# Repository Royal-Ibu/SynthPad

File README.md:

# SynthPad
A custom MIDI keypad with 6 Kalih Choc switches, an EC11 Rotary Encoder, a Bourns slide potentiometer, capacitive touch keys, and a Waveshare ESP32-S3-ZERO! SynthPad was made as a submission for Hack Club's Half-Life Week 3 Challenge - Music Projects!

## Renders

## Features

- Six Kailh Choc switches: Six low-profile mechanical keys for tactile input.
- EC11 rotary encoder: Provides rotary input and an integrated push-button input.
- Bourns slide potentiometer: Adds a sliding analog control for a MIDI parameter.
- Waveshare ESP32-S3-ZERO: Handles the controller's inputs and will run the MIDI firmware.
- Capacitive touch keys: Electronic touch pad switches for further inputs!

## Bill of Materials (BOM)

| Component | Quantity | Description | Part / model |
|---|---:|---|---|
| Kailh Choc switches | 6 | Low-profile mechanical key switches | Exact variant TBD |
| EC11 rotary encoder | 1 | Incremental rotary encoder with push-button input | Exact variant TBD |
| Bourns slide potentiometer | 1 | Linear slide potentiometer for analog input | Exact part number TBD |
| Waveshare ESP32-S3-ZERO | 1 | Main microcontroller board | ESP32-S3-ZERO |
| 1N4148 Diodes | 6 | Through-hole diodes, one per switch | TBD |

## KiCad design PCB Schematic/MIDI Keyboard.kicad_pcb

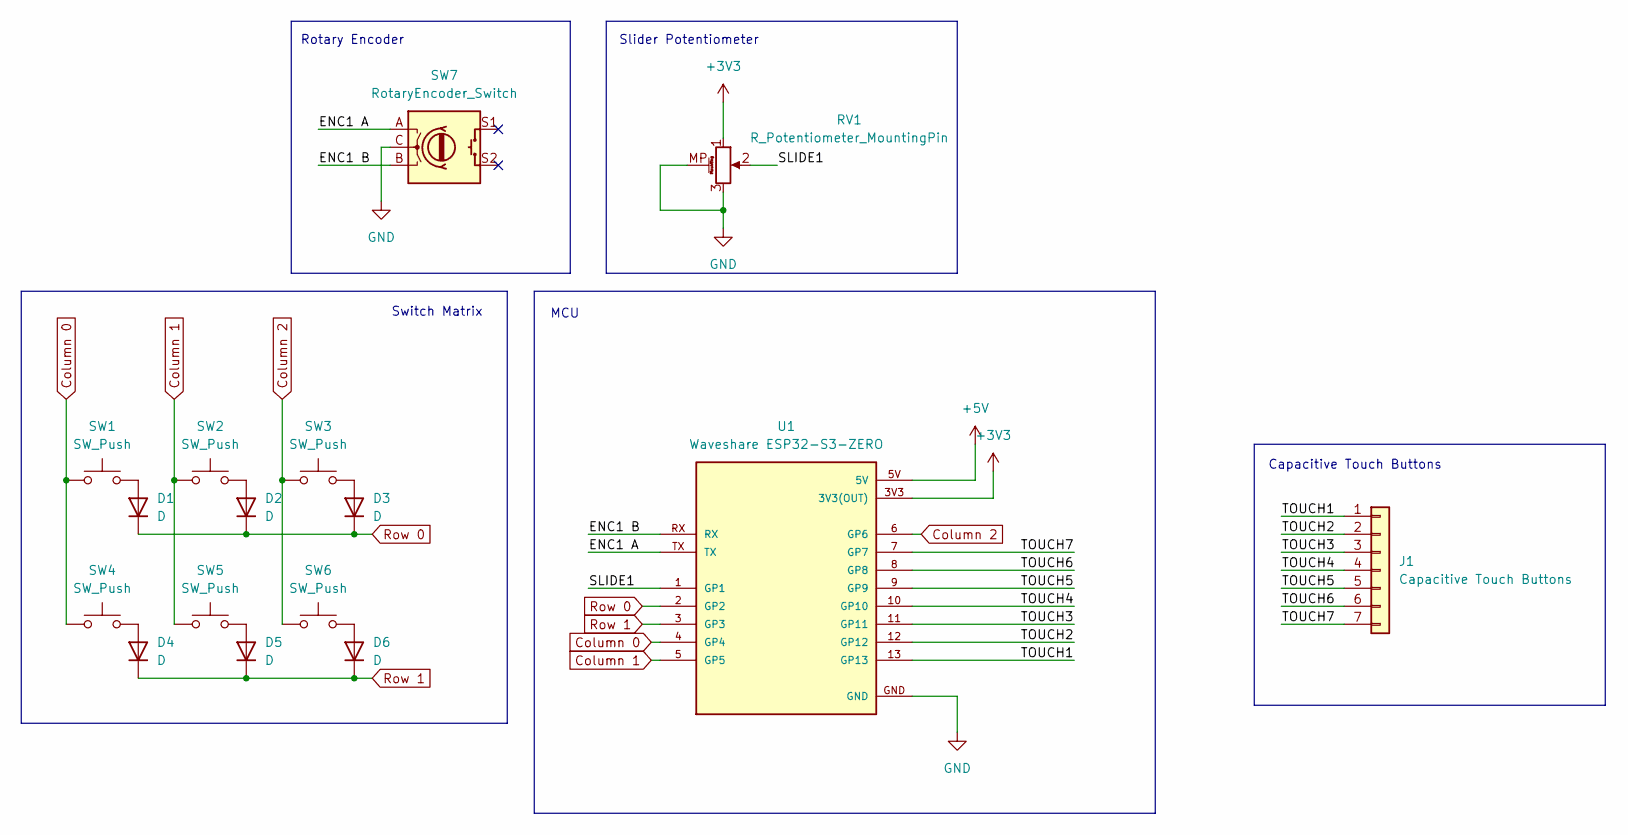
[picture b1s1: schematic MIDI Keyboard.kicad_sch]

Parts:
D1, D2, D3, D4, D5, D6: D; D_DO-35_SOD27_P7.62mm_Horizontal
J1: Capacitive Touch Buttons; Capacitive Keys
RV1: R_Potentiometer_MountingPin; Potentiometer_Bourns_PTA1543_Single_Slide
SW1, SW2, SW3, SW4, SW5, SW6: SW_Push; Kailh Choc Low-Profile Switches
SW7: RotaryEncoder_Switch; RotaryEncoder_Alps_EC11E-Switch_Vertical_H20mm
U1: Waveshare ESP32-S3-ZERO; Waveshare ESP32-S3-Zero; PARTREV NA

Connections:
+3V3: RV1.1, U1.3V3 (3V3(OUT))
+5V: U1.5V
/ENC1 A: SW7.A, U1.TX
/ENC1 B: SW7.B, U1.RX
/SLIDE1: RV1.2, U1.1 (GP1)
/TOUCH1: J1.1, U1.13 (GP13)
/TOUCH2: J1.2, U1.12 (GP12)
/TOUCH3: J1.3, U1.11 (GP11)
/TOUCH4: J1.4, U1.10 (GP10)
/TOUCH5: J1.5, U1.9 (GP9)
/TOUCH6: J1.6, U1.8 (GP8)
/TOUCH7: J1.7, U1.7 (GP7)
Column 0: SW1.1, SW4.1, U1.4 (GP4)
Column 1: SW2.1, SW5.1, U1.5 (GP5)
Column 2: SW3.1, SW6.1, U1.6 (GP6)
GND: RV1.3, RV1.MP (MountPin), SW7.C, U1.GND
unnamed: D1.2 (A), SW1.2
unnamed: D2.2 (A), SW2.2
unnamed: D3.2 (A), SW3.2
unnamed: D4.2 (A), SW4.2
unnamed: D5.2 (A), SW5.2
unnamed: D6.2 (A), SW6.2
Row 0: D1.1 (K), D2.1 (K), D3.1 (K), U1.2 (GP2)
Row 1: D4.1 (K), D5.1 (K), D6.1 (K), U1.3 (GP3)

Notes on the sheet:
Switch Matrix
Slider Potentiometer
Capacitive Touch Buttons
Rotary Encoder
MCU

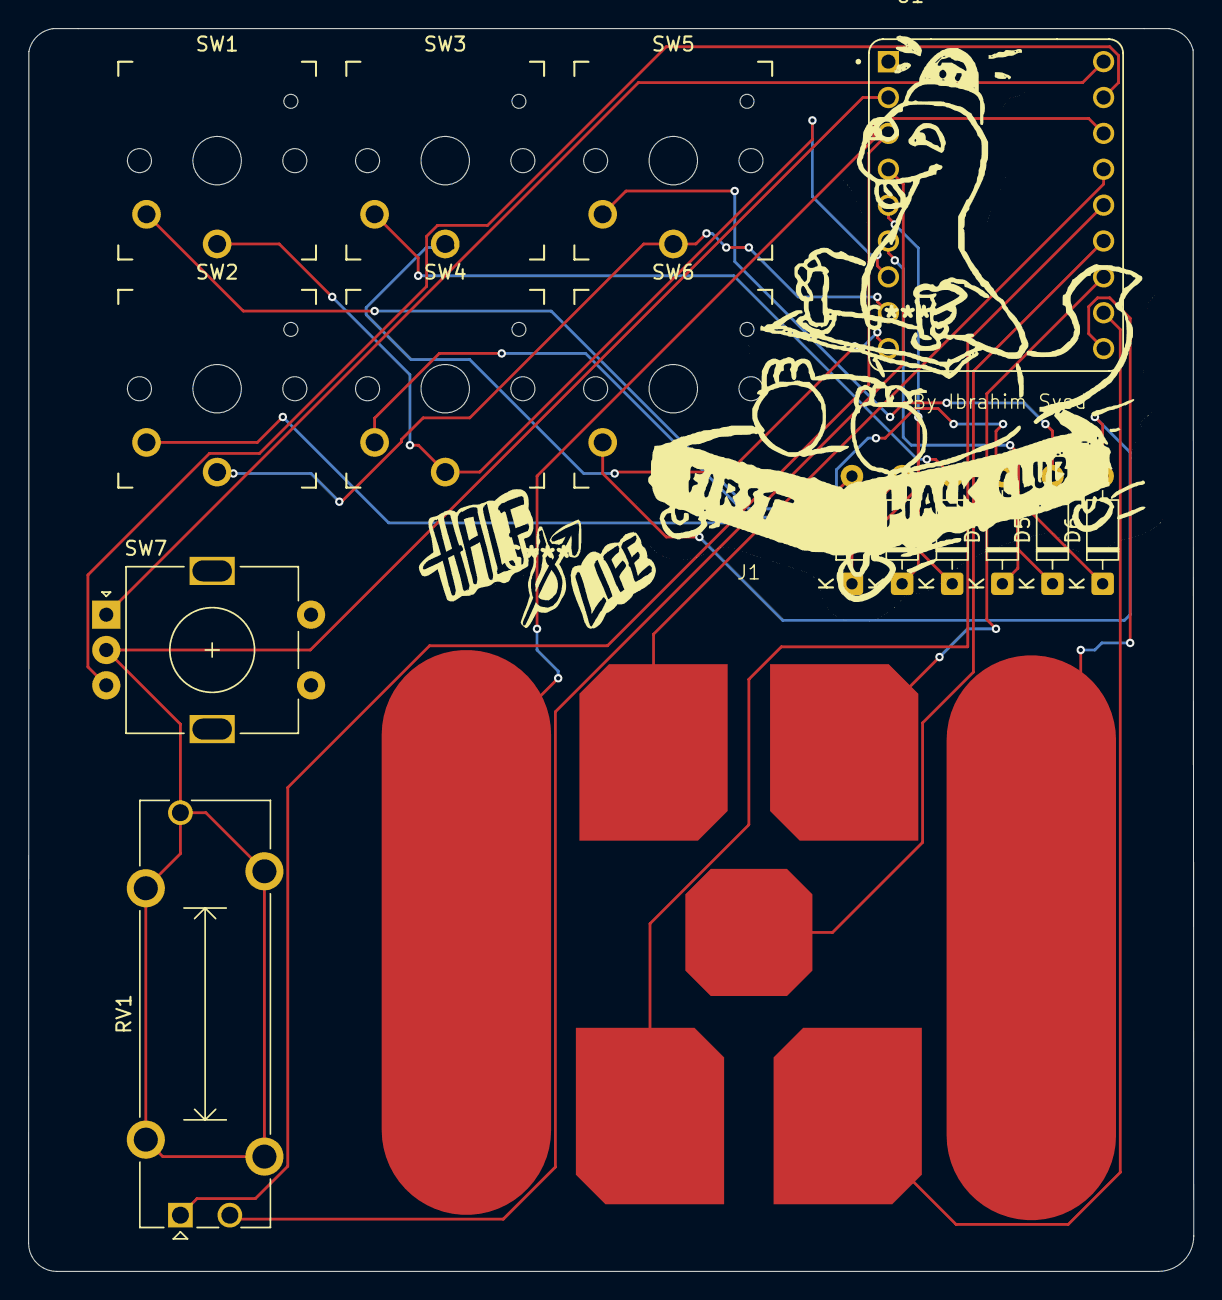
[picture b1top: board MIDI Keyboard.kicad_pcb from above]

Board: 2 copper layers, 82.5 x 88.0 mm, 16 parts (0 on the bottom side), 23 nets.
